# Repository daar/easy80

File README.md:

## Easy80

This repository contains all project files for the easy80 project. This project is about building a single board computer based on the 8 bit Z80 microprocessor, including an IDE that supports the development of new hardware and software. All software and hardware designs can be found here.

For more information see also: http://easy80blog.wordpress.com

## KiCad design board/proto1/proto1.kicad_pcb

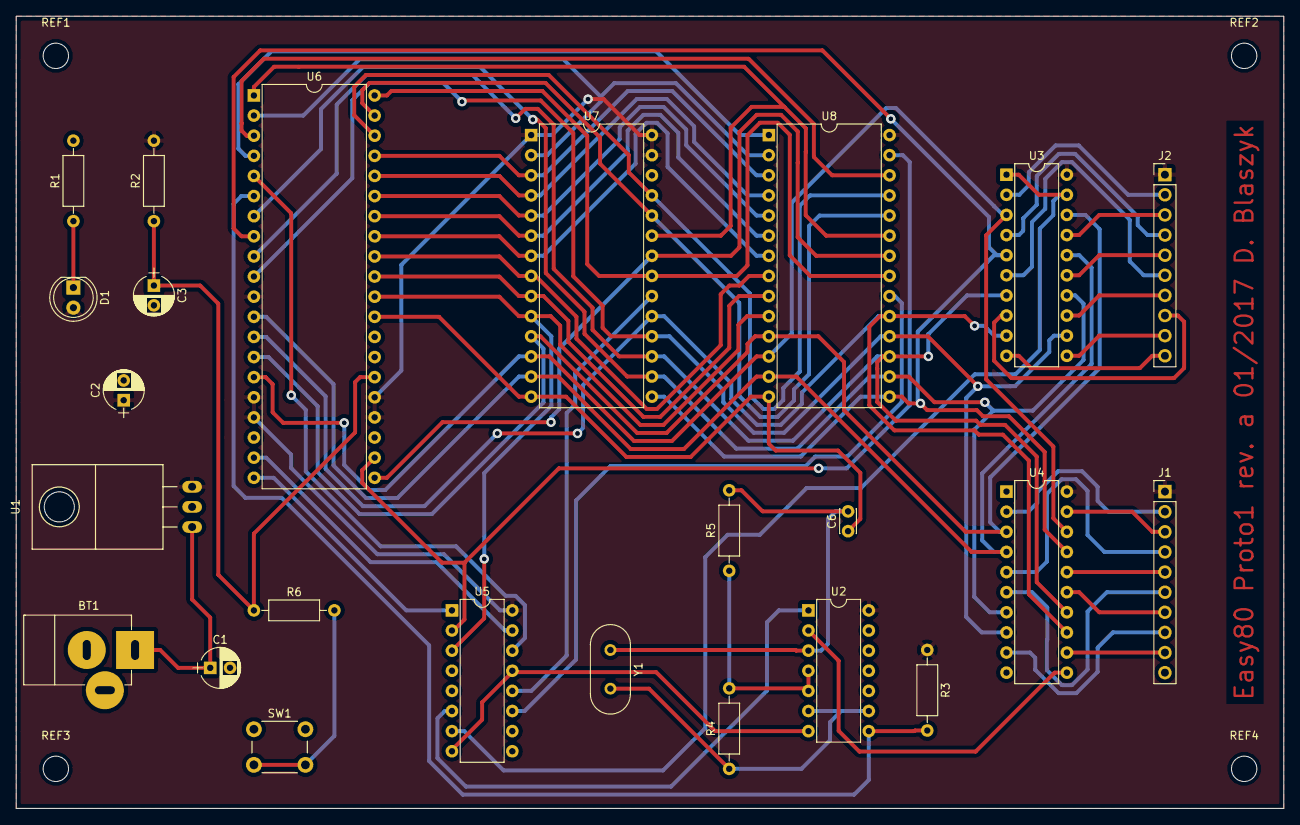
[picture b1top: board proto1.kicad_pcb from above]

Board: 2 copper layers, 160.0 x 100.0 mm, 28 parts (0 on the bottom side), 59 nets.

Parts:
BT1: Battery; JACK_ALIM
C1: 100uF; CP_Radial_D5.0mm_P2.50mm
C2, C3: 10uF; CP_Radial_D5.0mm_P2.50mm
C6: 100pF; C_Disc_D3.0mm_W2.0mm_P2.50mm
D1: LED; LED_D5.0mm
J1, J2: CONN_01X10; Pin_Header_Straight_1x10_Pitch2.54mm
R1, R3: 330; R_Axial_DIN0207_L6.3mm_D2.5mm_P10.16mm_Horizontal
R2, R6: 10K; R_Axial_DIN0207_L6.3mm_D2.5mm_P10.16mm_Horizontal
R4, R5: 1200; R_Axial_DIN0207_L6.3mm_D2.5mm_P10.16mm_Horizontal
REF1, REF2, REF3, REF4: MountingHole_3.2mm_M3
SW1: SW_Push; SW_PUSH_6mm
U1: LM7805CT; TO-220_Neutral123_Horizontal
U2: 74LS04; DIP-14_W7.62mm
U3: 74LS244; DIP-20_W7.62mm
U4: 74LS374; DIP-20_W7.62mm
U5: 74LS139; DIP-16_W7.62mm
U6: Z80CPU; DIP-40_W15.24mm
U7: 27C64; DIP-28_W15.24mm
U8: HM62256BLFP-7T; DIP-28_W15.24mm
Y1: 4 MHz; Crystal_HC49-U_Vertical

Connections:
/A0: U5.3, U6.30, U7.10, U8.10
/A1: U6.31, U7.9, U8.9
/A2: U6.32, U7.8, U8.8
/A3: U6.33, U7.7, U8.7
/A4: U6.34, U7.6, U8.6
/A5: U6.35, U7.5, U8.5
/A6: U6.36, U7.4, U8.4
/A7: U6.37, U7.3, U8.3
/A8: U6.38, U7.25, U8.25
/A9: U6.39, U7.24, U8.24
/A10: U6.40, U7.21, U8.21
/A11: U6.1, U7.23, U8.23
/A12: U6.2, U7.2, U8.2
/A13: U6.3, U8.26
/A14: U6.4, U8.1
/A15: U5.14, U6.5
/D0: U3.18, U4.3, U6.14, U7.11, U8.11
/D1: U3.3, U4.18, U6.15, U7.12, U8.12
/D2: U3.16, U4.4, U6.12, U7.13, U8.13
/D3: U3.5, U4.17, U6.8, U7.15, U8.15
/D4: U3.14, U4.7, U6.7, U7.16, U8.16
/D5: U3.7, U4.14, U6.9, U7.17, U8.17
/D6: U3.12, U4.8, U6.10, U7.18, U8.18
/D7: U3.9, U4.13, U6.13, U7.19, U8.19
GND: BT1.2, C1.2, C2.2, C3.2, C6.1, J1.10, J2.10, R1.2, SW1.1, U1.2, U2.7, U3.10, U4.1, U4.10, U5.8, U5.13, U6.29, U7.14, U8.14
unnamed: BT1.1, C1.1, U1.1
unnamed: C3.1, R2.1, R6.1, U6.26
unnamed: C6.2, R5.2, U2.3, Y1.1
unnamed: D1.1, R1.1
unnamed: R4.1, U2.6, U2.9, Y1.2
unnamed: R4.2, R5.1, U2.4, U2.5
unnamed: R6.2, SW1.2
unnamed: U2.2, U4.11
VCC: C2.1, D1.2, J1.1, J2.1, R2.2, R3.1, U1.3, U2.14, U3.20, U4.20, U5.16, U6.11, U6.16, U6.17, U6.24, U6.25, U7.1, U7.27, U7.28, U8.28
clock: R3.2, U2.8, U6.6
in0: J2.2, U3.2
in1: J2.3, U3.17
in2: J2.4, U3.4
in3: J2.5, U3.15
in4: J2.6, U3.6
in5: J2.7, U3.13
in6: J2.8, U3.8
in7: J2.9, U3.11
incs: U3.1, U3.19, U5.7
ioreq: U5.1, U6.20
mreq: U5.15, U6.19
o0: J1.2, U4.2
o1: J1.3, U4.19
o2: J1.4, U4.5
o3: J1.5, U4.16
o4: J1.6, U4.6
o5: J1.7, U4.15
o6: J1.8, U4.9
o7: J1.9, U4.12
outcs: U2.1, U5.6
ramcs: U5.11, U8.20
rd: U6.21, U7.22, U8.22
romcs: U5.12, U7.20
wr: U5.2, U6.22, U8.27

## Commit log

2016-12-14 committing all files from Mario added some text to the readme file
2016-12-18 adding project files for PROTO1, the first Z80 prototype board
2016-12-18 documentation for the boards, downloaded from different sources on the internet
2016-12-21 Adding PDFs
2017-01-04 Initial version of the easy80 IDE. This is still very basic and not much is working.
2017-01-07 Commit of first icons and icon registration tool icons_update. IDE: added splitter between editor screen and project filelist
2017-01-08 Initial commit for the i18n of the IDE Renamed some components
2017-01-08 initial commit of splashscreen
2017-01-13 added options dialog The language of the IDE can now be set by the user (needs restart of application) started implementation of hexviewer component
2017-01-14 Splash can be skipped at startup through command-line parameter --no-splash Implemented projectfiles management list Named all menu items logically Implemented Save/Save as/Save all for all editors
2017-01-14 fix typo
2017-01-14 Moved some strings to ResourceStrings
2017-01-17 adding the Z80 technical manual
2017-01-22 some small improvements in the tracks removed some redundant tracks recreated the PDF's
2017-01-29 Settings class based on RTTI for automatic saving of published properties Changed from ATBinHex to the KHexEditor library Implemented some settings for the hex editor Improved project file handling s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
2017-01-31 implemented option to reopen last projectfolder at startup MessageIntf: an interface class for IDE messages Delete files via the project file tree view ASMZ80: a native Z80 assembler (added the origi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
2017-02-04 reorganized layout for project treeview, it's now covering the whole left side of the form
2017-02-04 added popup menu for messages memo
2017-02-05 added kcontrols to GIT
2017-02-05 remove unneeded submodule atbinhex
2017-02-05 new folder tools hash_update: replaced batch script with pascal tool moved icons_update to tools added readme.txt on how to compile easy80-ide removed dependency on LazOpenGLContext
2017-02-05 forgot to remove OpenGLContext unit in main.pas
2017-02-05 replaced OptionsDialog with SettingsFrame, now the settings are part of the editor window Options are now called Settings some small fixes in readme.txt
2017-02-05 converted SplashScreen from TForm to TFrame
2017-02-05 start of documentation of the easy80-ide
2017-02-06 Adding a link to the github page
2017-02-06 major cleanup of settings use of non-default fonts throughout the application (win:Consola, linux:DejaVu Sans Mono, mac:Menlo)
2017-02-06 fixed small error in the font of settingsframe.lfm
2017-02-07 loading a default font in case not found removed some unused units
2017-02-07 added SynFacilSyn (submodule in external/SynFacilSyn) as new highlighter for assembler and pascal files highlighters are added as resource in the application re-implemented defaultfont, first try def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
2017-02-07 After changing SynFacilSyn to my local fork, and implementing a LoadFromResourceName method, the code can be simplified. A pull request was created to merge upstream.
2017-02-07 updated z80asm.xml file with z80 specific mnemonics and registers
2017-02-08 added submodule z80-pascal, which is a fork from the SVN project initial work on the Z80 pascal compiler changed external/SynFacilSyn to forked repository
2017-02-09 z80-pascal: easily exchangeable logging mechanism
2017-02-10 implemented quite some ProjectTreeView tools, accessible via popup menu - create new file - create new folder - rename file - duplicate file - delete file - add project folder - remove project folder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
2017-02-11 On delete file, the tab with the open file is closed now as well Changed some constant strings to resource strings Do not try to open an editor for root item Refactored code in actOpenInNewWindowExec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
2017-02-12 generic file icon
2017-02-12 initial import of a code library
2017-02-12 Added platform icons in README.md
2017-02-12 oops: fixed png images
2017-02-12 update board to eurocard size (160x100mm) and re-layout
2017-02-12 update board to eurocard size (160x100mm) and re-layout board and traces
2017-02-12 added Travis CI build scripts (thanks to: https://github.com/nielsAD/travis-lazarus)
2017-02-12 pushing travis-lazarus submodule
2017-02-12 added placeholders for all IDE modules
2017-02-12 Fixed type in the Travis-CI link
2017-02-12 setting permission for .travis.install.py
2017-02-12 updated build script
2017-02-12 fixed typo in build script
2017-02-12 Adding the FPC binary path
2017-12-26 -adding the C sources for pcb-editor, possibly this will make it into the easy80-ide some day -fixing kgrids for lazarus 1.8.0 -replace ICON_INFO with ICON_EASY80 in main.pas
2017-12-26 Update easy80-ide.de_DE.po (POEditor.com)
2017-12-26 added application icon
2017-12-26 Update easy80-ide.zh_CN.po (POEditor.com)
2017-12-26 Update easy80-ide.nl_NL.po (POEditor.com)
2017-12-26 Update easy80-ide.pl_PL.po (POEditor.com)
2017-12-26 Update easy80-ide.es_ES.po (POEditor.com)
